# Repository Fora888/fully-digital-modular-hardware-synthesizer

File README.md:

# Fully digital modular synthesizer
A fully digital modular synthesizer specification

## Specification

### Audio data format
The audio data is transmitted and processed at 44.1kHz sample rate and 16 Bits of resolution

### Data transmission
Data transmission utilizes UART in combination with a simple protocol.
UART is configured at a baud rate of 2,000,000 with 8 data bits, 1 stop bit, no flow control and regular polarity. Signal levels are defined as 0V for low and 3.3V for high. However, all inputs and outputs should withstand voltages from +12V to -12V to prevent accidental damage when interfaced with analog equipment.
Due to UART's limitation of transmitting only 8 bits at a time and each audio sample requiring 16 bits, each sample is transmitted as three sequential packets. Each packet consists of 6 data bits followed by 2 order bits. Therefore a full UART frame looks like the following:
|1|6|2|1|
|-|-|-|-|
|Start bit|Data bits|Order bits|Stop bit|

The least significant 8 bits of a sample are sent first with order bits '00', followed by the middle 8 bits with order bits '10', and finally the most significant 4 bits with order bits '01'. The last two data bits of the last packet with order bits '01', as well as the order bit combination '11', remain unused for now but could be utilized for future extensions.

### Power
Modules are connected to +5V and ground via a 6 pin, 2 row, 2.54mm (0.1 inch) spacing header connector. These use the following pinout:

| | | |
| ------------- | ------------- | --------- |
| 5v  | 5v  | GND |
| GND | GND | GND |

This asymmetric pattern ensures, that in case the header is plugged in incorrectly, the power supply is short-circuited  and the module doesn't get damaged. Therefore it is advisable for power supplys to feature some sort of fusing mechanism.
Since noisy power doesn't impact the sound quality of digital audio, switching power supplys are sufficient for voltage conversion

### Mechanical
Since UART necessitates only one cable for transmission, akin to mono audio, the mechanical specifications of virtually any existing analog modular synthesizer can be used. The examples are based on eurorack the eurorack specification with 128mm height and 3.5mm TS (mono) phone connectors.

## Comparison to analog

### Advantages
**Less noise** - Digital transmission ensures that the audio signal is received exactly as it was sent, without introducing noise during transmission. Furthermore many analog modules use analog-to-digital and digital-to-analog conversion, which introduce noise into the signal

**Reduced complexity** - Digital signals don't require clean power or buffering in order to deliver good audio. Merely two diodes and one or two resistors, which are always in the exact same configuration, are required per input or output. In addition all I/O is full 16 bit and the audio is inherently DC coupled.

**Lower Price** - Microprocessors are cheap and require relatively few and simple auxiliary components when compared to analog electronics. The reduced complexity of digital signal processing also leads to lower development costs.

### Disadvantages
**Latency** - Digital signal processing always comes with latency. In case of the examples, where audio is processed in blocks of 128 samples, this latency comes in at ~3 ms per module. Fast processors can however reduce the block size, reducing the latency to half of that or even less.

**Module selection** - The digital protocol described is still in its early stages of development and therefore there are no manufacturers for it yet. So the only way to use it is to build your own modules

## Implementations and examples
An implementation for the teensy audio library as well as several example modules can be found in the [Teensy](https://github.com/Fora888/fully-digital-modular-hardware-synthesizer/tree/main/Teensy) folder.

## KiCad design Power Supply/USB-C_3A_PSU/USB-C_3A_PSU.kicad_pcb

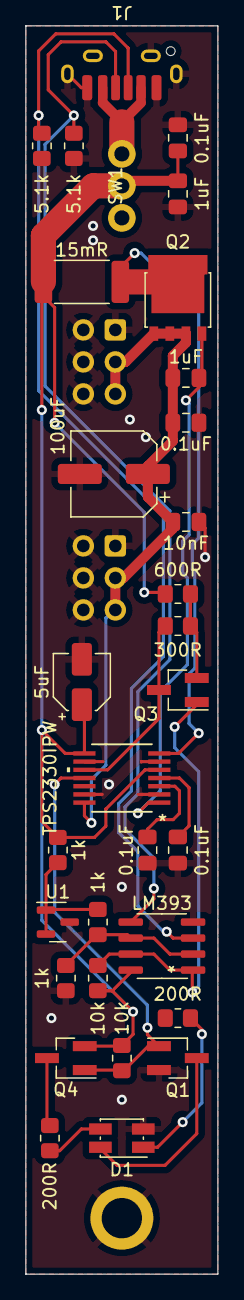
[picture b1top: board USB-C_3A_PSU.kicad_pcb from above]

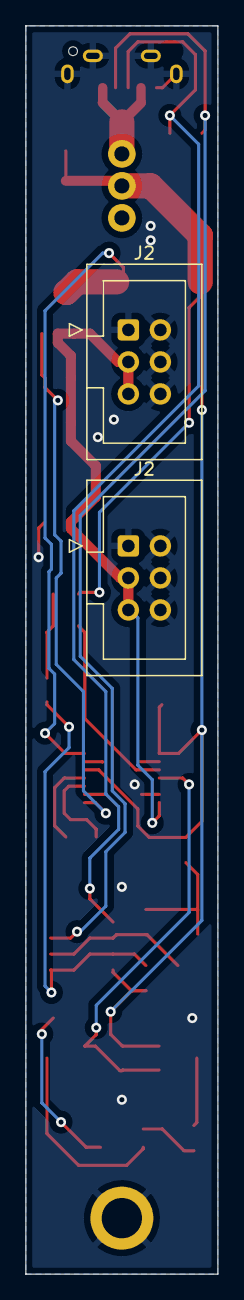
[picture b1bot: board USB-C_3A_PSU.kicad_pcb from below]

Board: 2 copper layers, 15.2 x 99.1 mm, 33 parts (2 on the bottom side), 20 nets.

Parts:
C1, C2, C4, C8: 0.1uF; C_0805_2012Metric_Pad1.18x1.45mm_HandSolder
C3, C5: 1uF; C_0805_2012Metric_Pad1.18x1.45mm_HandSolder
C6: 5uF; CP_Elec_4x5.4
C7: 10nF; C_0805_2012Metric_Pad1.18x1.45mm_HandSolder
C9: 100uF; CP_Elec_6.3x7.7
D1: LED_Dual_AKAK; LED_Kingbright_AAA3528ESGCT
J1: USB_C_Receptacle_USB2.0; USB_C_6Pin_Vert
J2, J2#2: Conn_02x03_Odd_Even; IDC-Header_2x03_P2.54mm_Vertical
Q1: Q_NMOS_GSD; SOT-23_Handsoldering
Q2: Q_NMOS_GSD; LFPAK56
Q3, Q4: Q_PMOS_GSD; SOT-23_Handsoldering
R1, R2: 5.1k; R_0805_2012Metric_Pad1.20x1.40mm_HandSolder
R3, R4, R5: 1k; R_0805_2012Metric_Pad1.20x1.40mm_HandSolder
R6, R12: 10k; R_0805_2012Metric_Pad1.20x1.40mm_HandSolder
R7: 15mR; R_2512_6332Metric_Pad1.40x3.35mm_HandSolder
R8: 600R; R_0805_2012Metric_Pad1.20x1.40mm_HandSolder
R9, R11: 200R; R_0805_2012Metric_Pad1.20x1.40mm_HandSolder
R10: 300R; R_0805_2012Metric_Pad1.20x1.40mm_HandSolder
SW1: SW_SPST; Miniature SPDT Toggle
U1: TL431DBZ; SOT-23
U2: LM393; SOIC-8_3.9x4.9mm_P1.27mm
U3: TPS2330IPW; PW14-M

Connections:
/1.25v Ref: R4.1, R5.1, U2.2 (-), U2.6 (_)
/5v In: C3.2, C4.2, C6.1, Q4.2 (S), R3.2, R6.1, R7.1, R8.1, R11.1, R12.2, SW1.2 (B), U2.8 (V+), U3.5 (VSENSE), U3.8 (IN)
/5v Out: C5.2, C7.1, C8.1, C9.1, J2.3, J2.5, J2#2.3, J2#2.5, Q2.2 (S), U3.14 (DISCH)
GND: C1.2, C2.2, C3.1, C4.1, C6.2, C7.2, C8.2, C9.2, D1.4 (K2), J1.A12 (GND), J1.B12 (GND), J1.S1 (SHIELD), J2.1, J2.2, J2.4, J2.6, J2#2.1, J2#2.2, J2#2.4, J2#2.6, Q1.2 (S), R1.2, R2.2, R5.2, U1.3 (A), U2.4 (V-), U3.2 (DGND), U3.6 (AGND), U3.9 (AGND), U3.13 (*ENABLE)
unnamed: C1.1, U3.3 (TIMER)
unnamed: C2.1, U3.4 (VREG)
unnamed: C5.1, Q2.1 (G), U3.1 (GATE)
unnamed: D1.1 (A1), R11.2
unnamed: D1.2 (K1), Q1.3 (D)
unnamed: D1.3 (A2), R9.2
unnamed: J1.A9 (VBUS), J1.B9 (VBUS), SW1.1 (A)
unnamed: J1.A5 (CC1), R2.1, U2.3 (+)
unnamed: J1.B5 (CC2), R1.1, U2.5 (+)
unnamed: Q1.1 (G), Q4.1 (G), R12.1, U3.11 (*FAULT)
unnamed: Q2.3 (D), R7.2, U3.7 (ISENSE)
unnamed: Q3.1 (G), R6.2, U2.1, U2.7
unnamed: Q3.2 (S), R8.2, R10.1
unnamed: Q3.3 (D), R10.2, U3.10 (ISET)
unnamed: Q4.3 (D), R9.1
unnamed: R3.1, R4.2, U1.1 (K), U1.2 (REF)

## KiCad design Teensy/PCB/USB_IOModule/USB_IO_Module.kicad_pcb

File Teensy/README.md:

# Teensy audio library extension
## TeensyDigitalModularExtension
This folder is a arduino library, which contains an implementation of the protocol as input and output blocks for the teensy audio library, as well as arduino sketches and auxiliary blocks for several example modules listed below. The library can easily be imported with the zip file and the following guide: https://docs.arduino.cc/software/ide-v1/tutorials/installing-libraries/.

## PCB
This folder contains PCBs as well as panel designs for the example modules. All PCBs use 2.54mm spacing between components, which means you can also build these modules on perfboard and connect the components with wire, instead of ordering PCBs

### VCA

### ADSR envelope generator

### Wavetable oscillator

### USB I/O

### Analog I/O

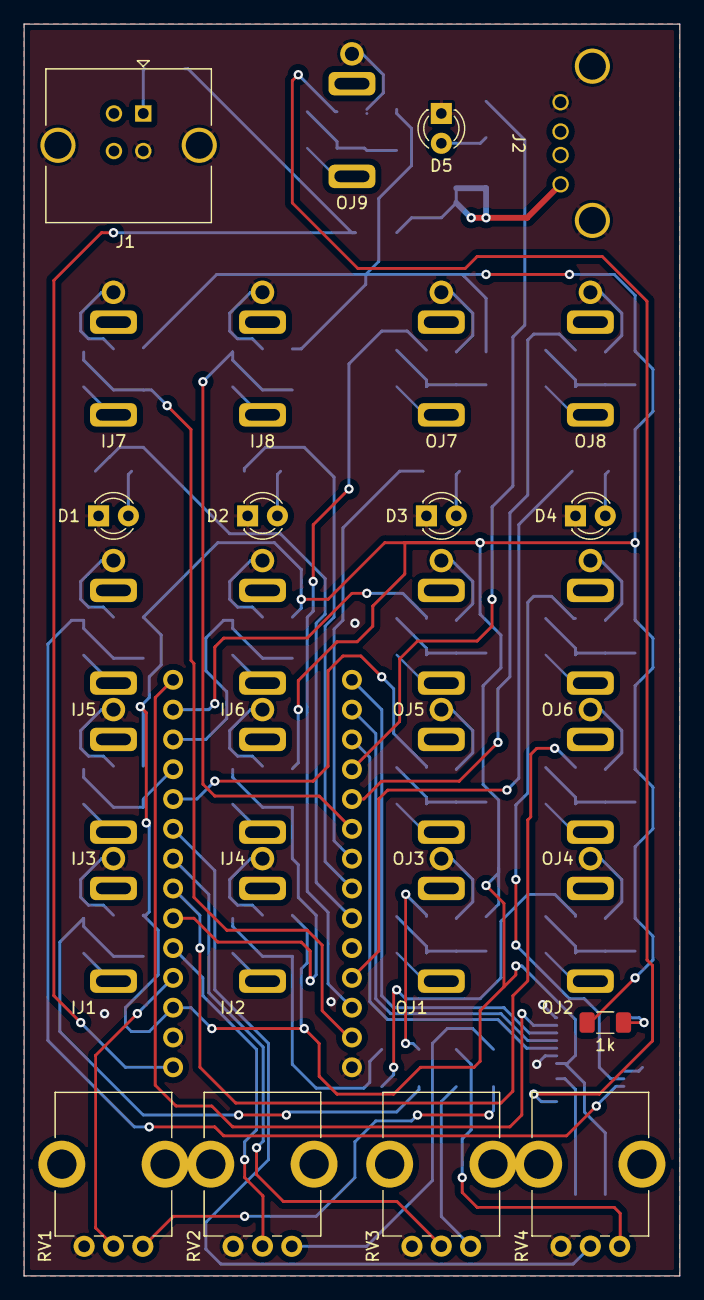
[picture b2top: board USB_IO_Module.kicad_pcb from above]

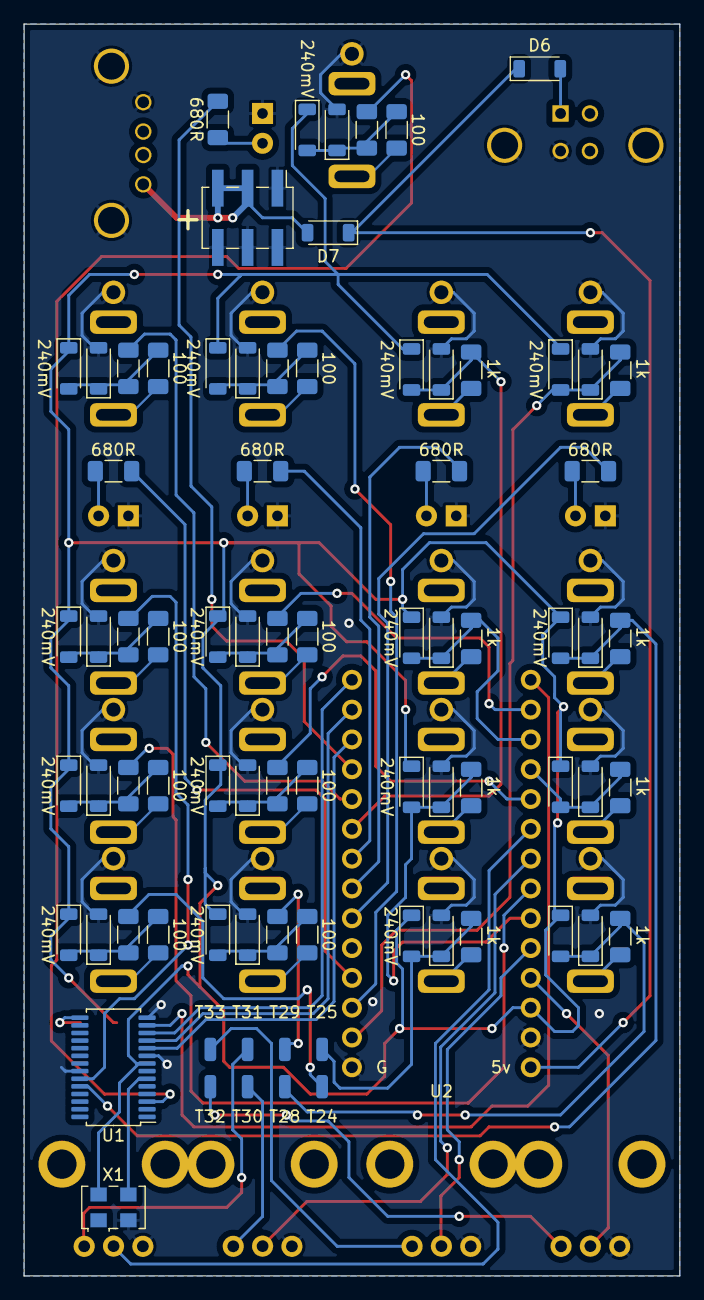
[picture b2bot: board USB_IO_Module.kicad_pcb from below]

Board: 2 copper layers, 55.9 x 106.7 mm, 101 parts (72 on the bottom side), 72 nets.

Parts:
D1, D2, D3, D4, D5: LED; LED_D3.0mm
D6, D7: 240mV; D_SOD-123 Handsolder
ID1, ID2, ID3, ID4, ID5, ID6, ID7, ID8, ID9, ID10, ID11, ID12, ID13, ID14, ID15, ID16: 240mV; D_SOD-123 Handsolder
IJ1, IJ2, IJ3, IJ4, IJ5, IJ6, IJ7, IJ8: Input; 3.5mm Jack Perfboard
IR1, IR2, IR3, IR4, IR5, IR6, IR7, IR8: 1k; R_1206_3216Metric_Pad1.30x1.75mm_HandSolder
J1: USB_B; USB_B_TE_5787834_Vertical
J2: USB_A; USB_A_Upright
J3: Power_Connector_2x3; PinHeader_2x03_P2.54mm_Vertical_SMD
OD1, OD2, OD3, OD4, OD5, OD6, OD7, OD8, OD9, OD10, OD11, OD12, OD13, OD14, OD15, OD16, OD17, OD18: 240mV; D_SOD-123 Handsolder
OJ1, OJ2, OJ3, OJ4, OJ5, OJ6, OJ7, OJ8, OJ9: Input; 3.5mm Jack Perfboard
OR1, OR3, OR5, OR7, OR9, OR11, OR13, OR15, OR17: 100; R_1206_3216Metric_Pad1.30x1.75mm_HandSolder
OR2, OR4, OR6, OR8, OR10, OR12, OR14, OR16, OR18: 900; R_1206_3216Metric_Pad1.30x1.75mm_HandSolder
R1: 1k; R_1206_3216Metric_Pad1.30x1.75mm_HandSolder
R2, R3, R4, R5, R6: 680R; R_1206_3216Metric_Pad1.30x1.75mm_HandSolder
RV1: Channel_1_Mod_Input_Gain; Bourns_PTV09A-4020UB103
RV2: Channel_2_Mod_Input_Gain; Bourns_PTV09A-4020UB103
RV3: Channel_1_Mod_Output_Gain; Bourns_PTV09A-4020UB103
RV4: Channel_2_Mod_Output_Gain; Bourns_PTV09A-4020UB103
U1: SC16IS762IPW; TSSOP-28_4.4x9.7mm_P0.65mm
U2: Teensy4.0; Teensy 4.0 horizontal
U2#2: Teensy4.0; Teensy 4.0 back pins
X1: XO53; Oscillator_SMD_EuroQuartz_XO53-4Pin_5.0x3.2mm

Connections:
+3.3V: ID2.1 (K), ID4.1 (K), ID6.1 (K), ID8.1 (K), ID10.1 (K), ID12.1 (K), ID14.1 (K), ID16.1 (K), OD2.1 (K), OD4.1 (K), OD6.1 (K), OD8.1 (K), OD10.1 (K), OD12.1 (K), OD14.1 (K), OD16.1 (K), OD18.1 (K), R1.1, U1.8 (VDD), U2.31 (3V3), X1.4 (V+)
+5V: D6.1 (K), D7.1 (K), U2.33 (VIN)
/RXB: ID9.1 (K), ID10.2 (A), IR5.2, U1.24 (RXB)
/T0: ID13.1 (K), ID14.2 (A), IR7.2, U2.2 (0_RX1_CRX2_CS1)
/T1: OR14.2, U2.3 (1_TX1_CTX2_MISO1)
/T2: R5.1, U2.4 (2_OUT2)
/T4: R2.1, U2.6 (4_BCLK2)
/T5: R3.1, U2.7 (5_IN2)
/T6: R4.1, U2.8 (6_OUT1D)
/T7: ID15.1 (K), ID16.2 (A), IR8.2, U2.9 (7_RX2_OUT1A)
/T8: OR16.2, U2.10 (8_TX2_IN1)
/T9: R6.1, U2.11 (9_OUT1C)
/T10: U1.10 (A0/~CS), U2.12 (10_CS_MQSR)
/T11: U1.11 (A1/SI), U2.13 (11_MOSI_CTX1)
/T12: U1.12 (n.c./SO), U2.14 (12_MISO_MQSL)
/T13: U1.13 (SCL/SCLK), U2.20 (13_SCK_CRX1_LED)
/T14: OR10.2, U2.21 (14_A0_TX3_SPDIF_OUT)
/T15: ID11.1 (K), ID12.2 (A), IR6.2, U2.22 (15_A1_RX3_SPDIF_IN)
/T16: ID5.1 (K), ID6.2 (A), IR3.2, U2.23 (16_A2_RX4_SCL1)
/T17: OR6.2, U2.24 (17_A3_TX4_SDA1)
/T18: RV4.2, U2.25 (18_A4_SDA0)
/T19: RV3.2, U2.26 (19_A5_SCL0)
/T20: OR8.2, U2.27 (20_A6_TX5_LRCLK1)
/T21: ID7.1 (K), ID8.2 (A), IR4.2, U2.28 (21_A7_RX5_BCLK1)
/T22: RV2.2, U2.29 (22_A8_CTX1)
/T23: RV1.2, U2.30 (23_A9_CRX1_MCLK1)
/T24: OR4.2, U2#2.35 (24_A10_TX6_SCL2)
/T25: ID3.1 (K), ID4.2 (A), IR2.2, U2#2.36 (25_A11_RX6_SDA2)
/T28: ID1.1 (K), ID2.2 (A), IR1.2, U2#2.39 (28_RX7)
/T29: OR2.2, U2#2.40 (29_TX7)
/T30: RV3.1, U2#2.41 (30_CRX3)
/T31: RV4.1, U2#2.42 (31_CTX3)
/T32: RV1.1, U2#2.43 (32_OUT1B)
/T33: RV2.1, U2#2.44 (33_MCLK2)
/TXA: OR18.2, U1.3 (TXA)
/TXB: OR12.2, U1.23 (TXB)
GND: D1.1 (K), D2.1 (K), D3.1 (K), D4.1 (K), D5.1 (K), ID1.2 (A), ID3.2 (A), ID5.2 (A), ID7.2 (A), ID9.2 (A), ID11.2 (A), ID13.2 (A), ID15.2 (A), IJ1.G, IJ2.G, IJ3.G, IJ4.G, IJ5.G, IJ6.G, IJ7.G, IJ8.G, J1.4 (GND), J1.5 (Shield), J2.4 (GND), J2.5 (Shield), J3.1, J3.2, J3.4, J3.6, OD1.2 (A), OD3.2 (A), OD5.2 (A), OD7.2 (A), OD9.2 (A), OD11.2 (A), OD13.2 (A), OD15.2 (A), OD17.2 (A), OJ1.G, OJ2.G, OJ3.G, OJ4.G, OJ5.G, OJ6.G, OJ7.G, OJ8.G, OJ9.G, RV1.3, RV2.3, RV3.3, RV4.3, U1.9 (I2C/~SPI), U1.14 (SDA/VSS), U1.22 (VSS), U2.1 (GND), U2.32 (GND), X1.2 (GND)
unnamed: D1.2 (A), R2.2
unnamed: D2.2 (A), R3.2
unnamed: D3.2 (A), R4.2
unnamed: D4.2 (A), R5.2
unnamed: D5.2 (A), R6.2
unnamed: D6.2 (A), J1.1 (VBUS)
unnamed: D7.2 (A), J2.1 (VBUS), J3.3, J3.5
unnamed: IJ1.T, IR1.1
unnamed: IJ2.T, IR2.1
unnamed: IJ3.T, IR3.1
unnamed: IJ4.T, IR4.1
unnamed: IJ5.T, IR5.1
unnamed: IJ6.T, IR6.1
unnamed: IJ7.T, IR7.1
unnamed: IJ8.T, IR8.1
unnamed: OD1.1 (K), OD2.2 (A), OR1.2, OR2.1
unnamed: OD3.1 (K), OD4.2 (A), OR3.2, OR4.1
unnamed: OD5.1 (K), OD6.2 (A), OR5.2, OR6.1
unnamed: OD7.1 (K), OD8.2 (A), OR7.2, OR8.1
unnamed: OD9.1 (K), OD10.2 (A), OR9.2, OR10.1
unnamed: OD11.1 (K), OD12.2 (A), OR11.2, OR12.1
unnamed: OD13.1 (K), OD14.2 (A), OR13.2, OR14.1
unnamed: OD15.1 (K), OD16.2 (A), OR15.2, OR16.1
unnamed: OD17.1 (K), OD18.2 (A), OR17.2, OR18.1
unnamed: OJ1.T, OR1.1
unnamed: OJ2.T, OR3.1
unnamed: OJ3.T, OR5.1
unnamed: OJ4.T, OR7.1
unnamed: OJ5.T, OR9.1
unnamed: OJ6.T, OR11.1
unnamed: OJ7.T, OR13.1
unnamed: OJ8.T, OR15.1
unnamed: OJ9.T, OR17.1
unnamed: R1.2, U1.15 (~IRQ)
unnamed: U1.6 (XTAL1), X1.3 (OUT)

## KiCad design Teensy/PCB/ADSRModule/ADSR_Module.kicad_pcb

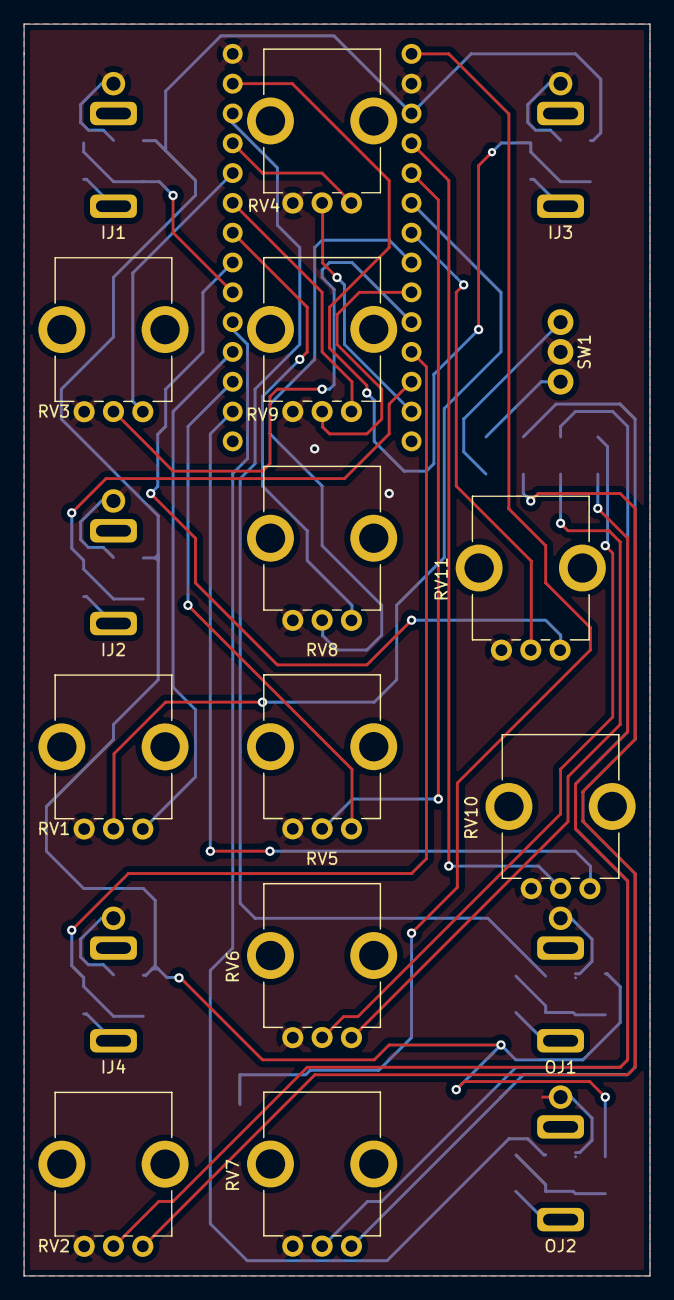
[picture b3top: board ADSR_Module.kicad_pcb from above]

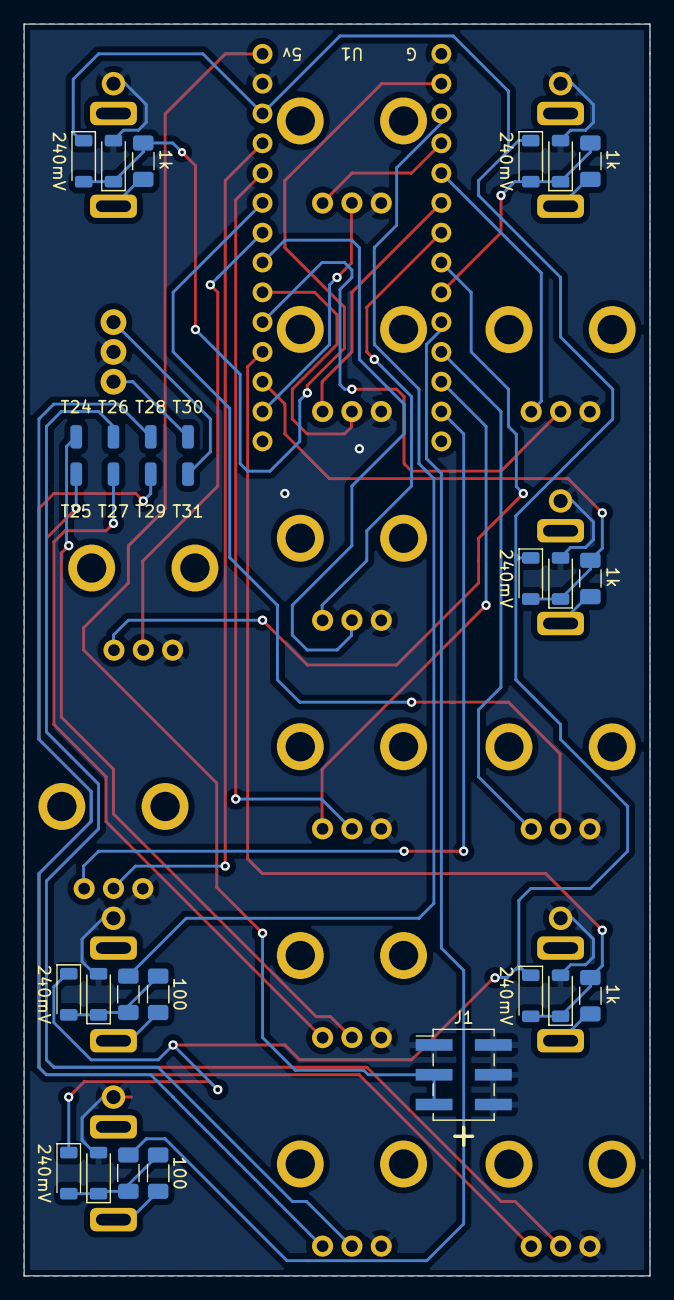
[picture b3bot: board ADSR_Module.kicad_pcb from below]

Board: 2 copper layers, 53.3 x 106.7 mm, 41 parts (23 on the bottom side), 41 nets.

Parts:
ID1, ID2, ID3, ID4, ID5, ID6, ID7, ID8: 240mV; D_SOD-123 Handsolder
IJ1, IJ2, IJ3, IJ4: Input; 3.5mm Jack Perfboard
IR1, IR2, IR3, IR4: 1k; R_1206_3216Metric_Pad1.30x1.75mm_HandSolder
J1: Power_Connector_2x3; PinHeader_2x03_P2.54mm_Vertical_SMD
OD1, OD2, OD3, OD4: 240mV; D_SOD-123 Handsolder
OJ1, OJ2: Input; 3.5mm Jack Perfboard
OR1, OR3: 100; R_1206_3216Metric_Pad1.30x1.75mm_HandSolder
OR2, OR4: 900; R_1206_3216Metric_Pad1.30x1.75mm_HandSolder
RV1: Decay_Time_Mod_Scale; Bourns_PTV09A-4020UB103
RV2: Release_Time_Mod_Scale; Bourns_PTV09A-4020UB103
RV3: Attack_Time_Mod_Scale; Bourns_PTV09A-4020UB103
RV4: Attack_Slope; Bourns_PTV09A-4020UB103
RV5: Decay_Time_Offset; Bourns_PTV09A-4025FB103
RV6: Release_Slope; Bourns_PTV09A-4020UB103
RV7: Release_Time_Offset; Bourns_PTV09A-4025FB103
RV8: Decay_Slope; Bourns_PTV09A-4020UB103
RV9: Attack_Time_Offset; Bourns_PTV09A-4025FB103
RV10: Output_Scale; Bourns_PTV09A-4020UB103
RV11: Sustain_Offset; Bourns_PTV09A-4020UB103
SW1: Mode_Switch; Miniature SPDT Toggle
U1: Teensy4.0; Teensy 4.0 horizontal
U1#2: Teensy4.0; Teensy 4.0 back pins

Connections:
+3.3V: ID2.1 (K), ID4.1 (K), ID6.1 (K), ID8.1 (K), OD2.1 (K), OD4.1 (K), U1.31 (3V3)
+5V: J1.3, J1.5, U1.33 (VIN)
/T0: ID5.1 (K), ID6.2 (A), IR3.2, U1.2 (0_RX1_CRX2_CS1)
/T1: OR2.2, U1.3 (1_TX1_CTX2_MISO1)
/T2: RV4.1, U1.4 (2_OUT2)
/T3: RV3.1, U1.5 (3_LRCLK2)
/T4: RV9.1, U1.6 (4_BCLK2)
/T5: RV8.1, U1.7 (5_IN2)
/T6: RV11.1, U1.8 (6_OUT1D)
/T7: ID1.1 (K), ID2.2 (A), IR1.2, U1.9 (7_RX2_OUT1A)
/T8: OR4.2, U1.10 (8_TX2_IN1)
/T9: RV1.1, U1.11 (9_OUT1C)
/T10: RV5.1, U1.12 (10_CS_MQSR)
/T11: RV10.1, U1.13 (11_MOSI_CTX1)
/T14: RV4.2, U1.21 (14_A0_TX3_SPDIF_OUT)
/T15: ID3.1 (K), ID4.2 (A), IR2.2, U1.22 (15_A1_RX3_SPDIF_IN)
/T16: ID7.1 (K), ID8.2 (A), IR4.2, U1.23 (16_A2_RX4_SCL1)
/T17: RV3.2, U1.24 (17_A3_TX4_SDA1)
/T18: RV9.2, U1.25 (18_A4_SDA0)
/T19: RV8.2, U1.26 (19_A5_SCL0)
/T20: RV11.2, U1.27 (20_A6_TX5_LRCLK1)
/T21: RV1.2, U1.28 (21_A7_RX5_BCLK1)
/T22: RV5.2, U1.29 (22_A8_CTX1)
/T23: RV10.2, U1.30 (23_A9_CRX1_MCLK1)
/T24: RV6.2, U1#2.35 (24_A10_TX6_SCL2)
/T25: RV2.2, U1#2.36 (25_A11_RX6_SDA2)
/T26: RV7.2, U1#2.37 (26_A12_MOSI1)
/T27: RV6.1, U1#2.38 (27_A13_SCK1)
/T28: RV7.1, U1#2.39 (28_RX7)
/T29: RV2.1, U1#2.40 (29_TX7)
/T30: SW1.3, U1#2.41 (30_CRX3)
/T31: SW1.1, U1#2.42 (31_CTX3)
GND: ID1.2 (A), ID3.2 (A), ID5.2 (A), ID7.2 (A), IJ1.G, IJ2.G, IJ3.G, IJ4.G, J1.1, J1.2, J1.4, J1.6, OD1.2 (A), OD3.2 (A), OJ1.G, OJ2.G, RV1.3, RV2.3, RV3.3, RV4.3, RV5.3, RV6.3, RV7.3, RV8.3, RV9.3, RV10.3, RV11.3, SW1.2, U1.1 (GND), U1.32 (GND)
unnamed: IJ1.T, IR1.1
unnamed: IJ2.T, IR2.1
unnamed: IJ3.T, IR3.1
unnamed: IJ4.T, IR4.1
unnamed: OD1.1 (K), OD2.2 (A), OR1.2, OR2.1
unnamed: OD3.1 (K), OD4.2 (A), OR3.2, OR4.1
unnamed: OJ1.T, OR1.1
unnamed: OJ2.T, OR3.1

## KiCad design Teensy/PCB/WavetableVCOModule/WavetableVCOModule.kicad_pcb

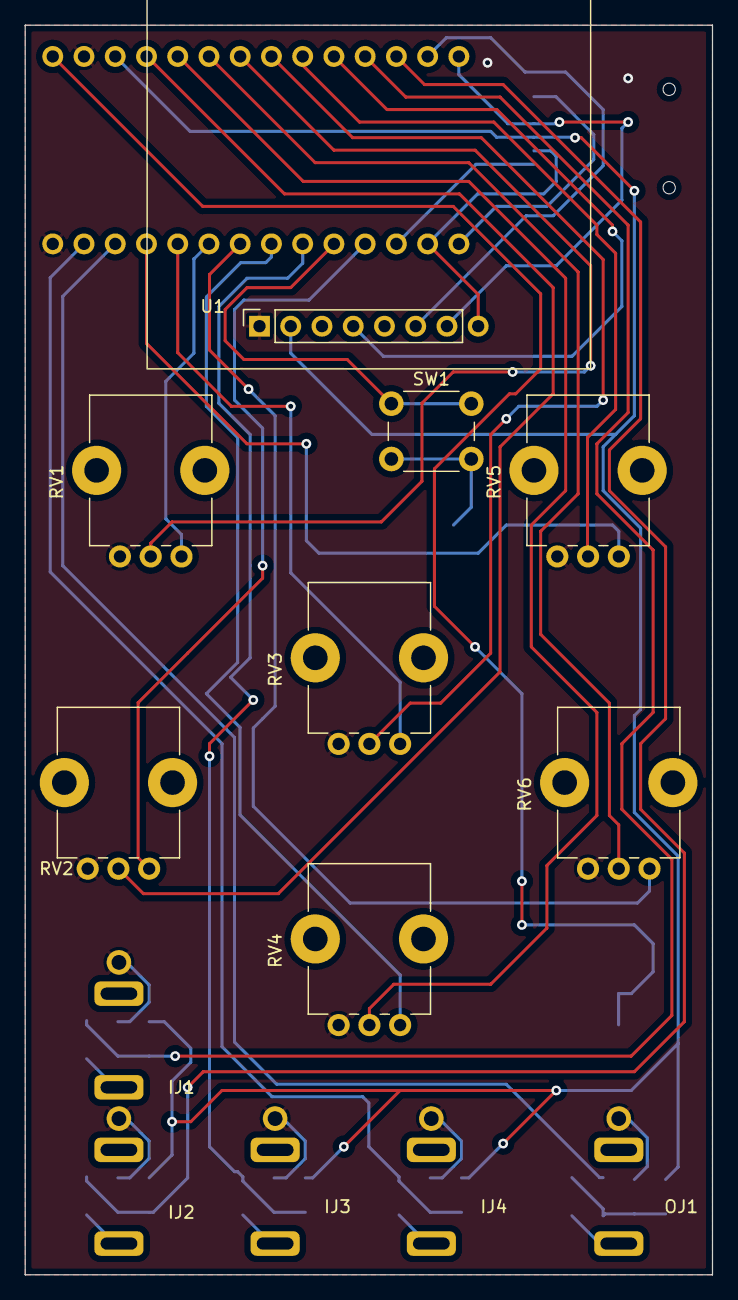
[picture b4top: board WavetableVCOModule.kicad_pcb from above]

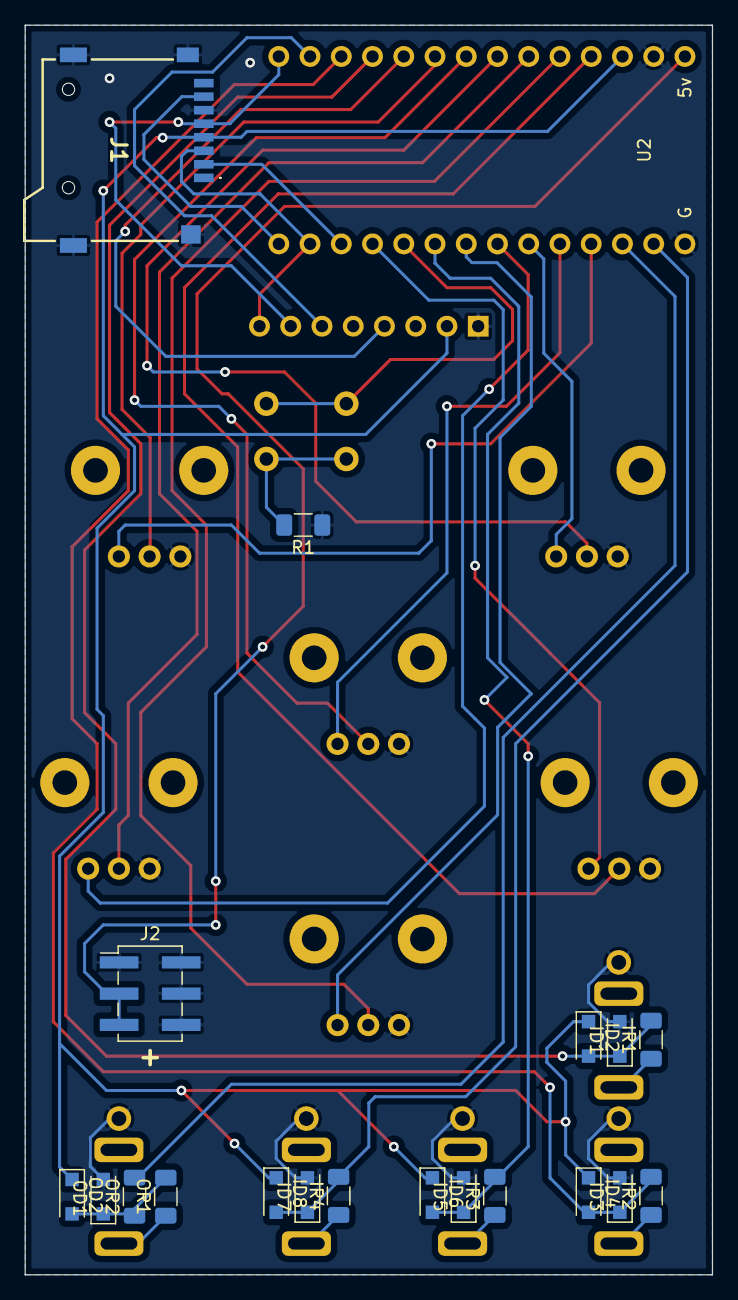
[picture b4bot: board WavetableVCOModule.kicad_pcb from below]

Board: 2 copper layers, 55.9 x 101.6 mm, 33 parts (20 on the bottom side), 34 nets.

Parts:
ID1, ID2, ID3, ID4, ID5, ID6, ID7, ID8: 240mV; D_SOD-123F
IJ1, IJ2, IJ3, IJ4: Input; 3.5mm Jack Perfboard
IR1, IR2, IR3, IR4: 1k; R_1206_3216Metric_Pad1.30x1.75mm_HandSolder
J1: Micro_SD_Card; MSD4A
J2: Power_Connector_2x3; PinHeader_2x03_P2.54mm_Vertical_SMD
OD1, OD2: 240mV; D_SOD-123F
OJ1: Input; 3.5mm Jack Perfboard
OR1: 100; R_1206_3216Metric_Pad1.30x1.75mm_HandSolder
OR2: 900; R_1206_3216Metric_Pad1.30x1.75mm_HandSolder
R1: 10k; R_1206_3216Metric_Pad1.30x1.75mm_HandSolder
RV1: Warp_Offset_Pot; Bourns_PTV09A-4025FB103
RV2: Warp_Scale_Pot; Bourns_PTV09A-4020UB103
RV3: Frequency_Offset_Pot; Bourns_PTV09A-4025FB103
RV4: FM_Scale_Pot; Bourns_PTV09A-4020UB103
RV5: Position_Offset_Pot; Bourns_PTV09A-4025FB103
RV6: Position_Scale_Pot; Bourns_PTV09A-4020UB103
SW1: Next_File_Button; SW_PUSH_6mm_H13mm
U1: SPI_Oled; 1.5_inch_Oled
U2: Teensy4.0; Teensy 4.0 horizontal

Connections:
+3.3V: ID2.1 (K), ID4.1 (K), ID6.1 (K), ID8.1 (K), J1.4 (VDD), OD2.1 (K), U1.6 (VIN), U2.31 (3V3)
+5V: J2.3, J2.5, U2.33 (VIN)
/T0: ID7.1 (K), ID8.2 (A), IR4.2, U2.2 (0_RX1_CRX2_CS1)
/T1: OR2.2, U2.3 (1_TX1_CTX2_MISO1)
/T2: RV5.1, U2.4 (2_OUT2)
/T3: RV3.1, U2.5 (3_LRCLK2)
/T4: RV1.1, U2.6 (4_BCLK2)
/T5: RV6.1, U2.7 (5_IN2)
/T6: RV4.1, U2.8 (6_OUT1D)
/T7: ID5.1 (K), ID6.2 (A), IR3.2, U2.9 (7_RX2_OUT1A)
/T8: SW1.1, U2.10 (8_TX2_IN1)
/T9: RV2.1, U2.11 (9_OUT1C)
/T10: J1.2 (DAT3/CD), U2.12 (10_CS_MQSR)
/T11: J1.3 (CMD), U1.1 (DATA), U2.13 (11_MOSI_CTX1)
/T12: J1.7 (DAT0), U2.14 (12_MISO_MQSL)
/T13: J1.5 (CLK), U1.2 (CLK), U2.20 (13_SCK_CRX1_LED)
/T14: U1.3 (D/C), U2.21 (14_A0_TX3_SPDIF_OUT)
/T15: ID3.1 (K), ID4.2 (A), IR2.2, U2.22 (15_A1_RX3_SPDIF_IN)
/T16: ID1.1 (K), ID2.2 (A), IR1.2, U2.23 (16_A2_RX4_SCL1)
/T17: U1.5 (CS), U2.24 (17_A3_TX4_SDA1)
/T18: RV5.2, U2.25 (18_A4_SDA0)
/T19: RV3.2, U2.26 (19_A5_SCL0)
/T20: RV1.2, U2.27 (20_A6_TX5_LRCLK1)
/T21: RV6.2, U2.28 (21_A7_RX5_BCLK1)
/T22: RV4.2, U2.29 (22_A8_CTX1)
/T23: RV2.2, U2.30 (23_A9_CRX1_MCLK1)
GND: ID1.2 (A), ID3.2 (A), ID5.2 (A), ID7.2 (A), IJ1.G, IJ2.G, IJ3.G, IJ4.G, J1.6 (VSS), J1.9 (SHIELD), J2.1, J2.2, J2.4, J2.6, OD1.2 (A), OJ1.G, R1.1, RV1.3, RV2.3, RV3.3, RV4.3, RV5.3, RV6.3, U1.7 (GND), U2.1 (GND), U2.32 (GND)
unnamed: IJ1.T, IR1.1
unnamed: IJ2.T, IR2.1
unnamed: IJ3.T, IR3.1
unnamed: IJ4.T, IR4.1
unnamed: OD1.1 (K), OD2.2 (A), OR1.2, OR2.1
unnamed: OJ1.T, OR1.1
unnamed: R1.2, SW1.2

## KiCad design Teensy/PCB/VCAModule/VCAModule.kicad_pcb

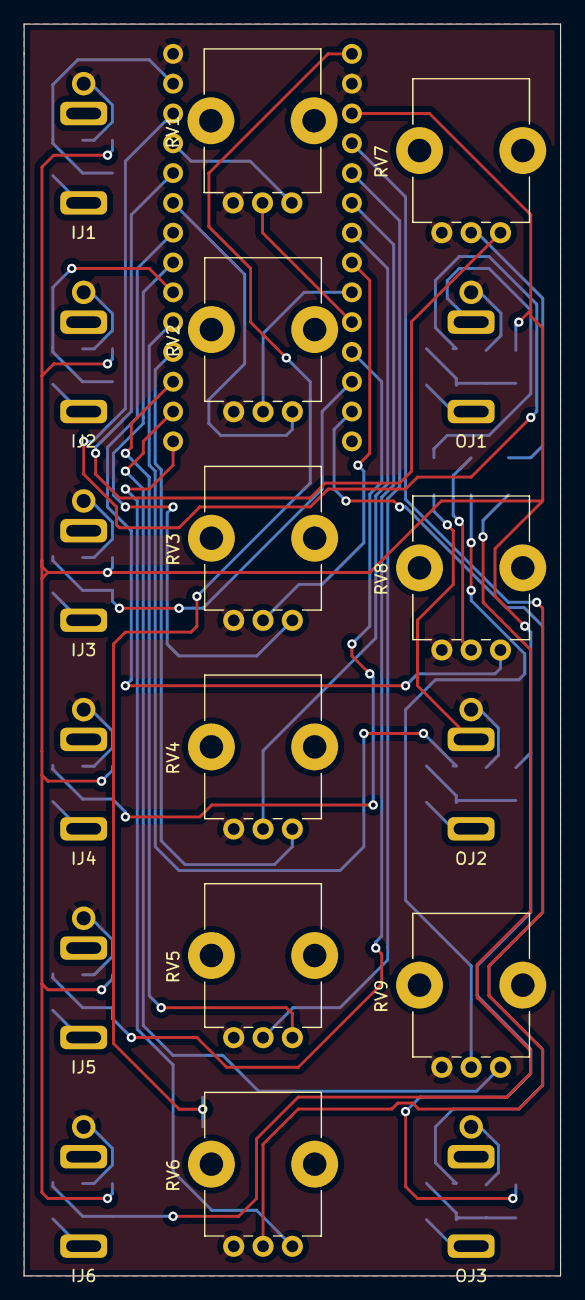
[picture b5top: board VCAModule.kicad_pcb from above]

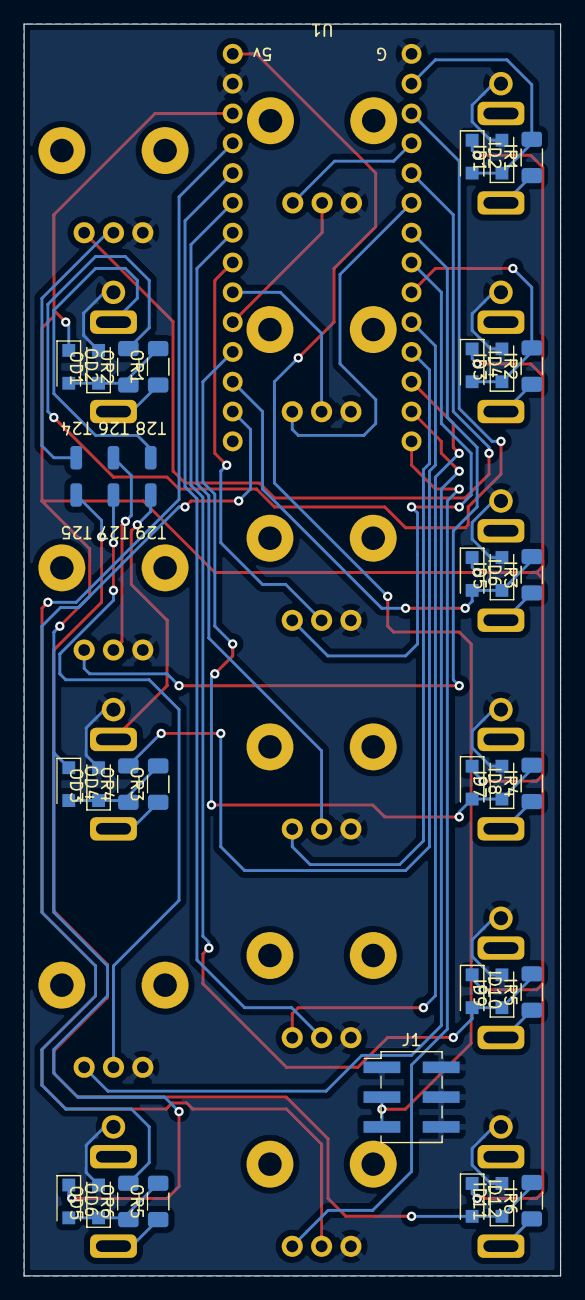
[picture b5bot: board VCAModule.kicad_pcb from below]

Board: 2 copper layers, 45.7 x 106.7 mm, 51 parts (33 on the bottom side), 44 nets.

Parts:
ID1, ID2, ID3, ID4, ID5, ID6, ID7, ID8, ID9, ID10, ID11, ID12: 240mV; D_SOD-123F
IJ1, IJ2, IJ3, IJ4, IJ5, IJ6: Input; 3.5mm Jack Perfboard
IR1, IR2, IR3, IR4, IR5, IR6: 1k; R_1206_3216Metric_Pad1.30x1.75mm_HandSolder
J1: Power_Connector_2x3; PinHeader_2x03_P2.54mm_Vertical_SMD
OD1, OD2, OD3, OD4, OD5, OD6: 240mV; D_SOD-123F
OJ1, OJ2, OJ3: Input; 3.5mm Jack Perfboard
OR1, OR3, OR5: 100; R_1206_3216Metric_Pad1.30x1.75mm_HandSolder
OR2, OR4, OR6: 900; R_1206_3216Metric_Pad1.30x1.75mm_HandSolder
RV1: CV_1_Slope; Bourns_PTV09A-4020UB103
RV2: CV_Scale_1; Bourns_PTV09A-4020UB103
RV3: CV_2_Slope; Bourns_PTV09A-4020UB103
RV4: CV_Scale_2; Bourns_PTV09A-4020UB103
RV5: CV_3_Slope; Bourns_PTV09A-4020UB103
RV6: CV_Scale_3; Bourns_PTV09A-4020UB103
RV7: VCA_1_Gain; Bourns_PTV09A-4025FB103
RV8: VCA_2_Gain; Bourns_PTV09A-4025FB103
RV9: VCA_3_Gain; Bourns_PTV09A-4025FB103
U1: Teensy4.0; Teensy 4.0 horizontal
U1#2: Teensy4.0; Teensy 4.0 back pins

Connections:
+3.3V: ID2.1 (K), ID4.1 (K), ID6.1 (K), ID8.1 (K), ID10.1 (K), ID12.1 (K), OD2.1 (K), OD4.1 (K), OD6.1 (K), U1.31 (3V3)
+5V: J1.3, J1.5, U1.33 (VIN)
/T0: ID1.1 (K), ID2.2 (A), IR1.2, U1.2 (0_RX1_CRX2_CS1)
/T1: OR2.2, U1.3 (1_TX1_CTX2_MISO1)
/T2: RV1.1, U1.4 (2_OUT2)
/T3: RV7.1, U1.5 (3_LRCLK2)
/T4: RV2.1, U1.6 (4_BCLK2)
/T5: RV8.1, U1.7 (5_IN2)
/T6: RV3.1, U1.8 (6_OUT1D)
/T7: ID3.1 (K), ID4.2 (A), IR2.2, U1.9 (7_RX2_OUT1A)
/T8: OR4.2, U1.10 (8_TX2_IN1)
/T9: RV4.1, U1.11 (9_OUT1C)
/T10: RV5.1, U1.12 (10_CS_MQSR)
/T11: RV9.1, U1.13 (11_MOSI_CTX1)
/T12: RV6.1, U1.14 (12_MISO_MQSL)
/T14: OR6.2, U1.21 (14_A0_TX3_SPDIF_OUT)
/T15: ID5.1 (K), ID6.2 (A), IR3.2, U1.22 (15_A1_RX3_SPDIF_IN)
/T16: ID7.1 (K), ID8.2 (A), IR4.2, U1.23 (16_A2_RX4_SCL1)
/T17: RV1.2, U1.24 (17_A3_TX4_SDA1)
/T18: RV2.2, U1.25 (18_A4_SDA0)
/T19: RV3.2, U1.26 (19_A5_SCL0)
/T20: RV4.2, U1.27 (20_A6_TX5_LRCLK1)
/T21: ID9.1 (K), ID10.2 (A), IR5.2, U1.28 (21_A7_RX5_BCLK1)
/T22: RV5.2, U1.29 (22_A8_CTX1)
/T23: RV6.2, U1.30 (23_A9_CRX1_MCLK1)
/T24: RV7.2, U1#2.35 (24_A10_TX6_SCL2)
/T25: ID11.1 (K), ID12.2 (A), IR6.2, U1#2.36 (25_A11_RX6_SDA2)
/T26: RV8.2, U1#2.37 (26_A12_MOSI1)
/T27: RV9.2, U1#2.38 (27_A13_SCK1)
/T28: OJ1.S, U1#2.39 (28_RX7)
/T29: OJ2.S, U1#2.40 (29_TX7)
GND: ID1.2 (A), ID3.2 (A), ID5.2 (A), ID7.2 (A), ID9.2 (A), ID11.2 (A), IJ1.G, IJ2.G, IJ3.G, IJ4.G, IJ5.G, IJ6.G, J1.1, J1.2, J1.4, J1.6, OD1.2 (A), OD3.2 (A), OD5.2 (A), OJ1.G, OJ2.G, OJ3.G, RV1.3, RV2.3, RV3.3, RV4.3, RV5.3, RV6.3, RV7.3, RV8.3, RV9.3, U1.1 (GND), U1.32 (GND)
unnamed: IJ1.T, IR1.1
unnamed: IJ2.T, IR2.1
unnamed: IJ3.T, IR3.1
unnamed: IJ4.T, IR4.1
unnamed: IJ5.T, IR5.1
unnamed: IJ6.T, IR6.1
unnamed: OD1.1 (K), OD2.2 (A), OR1.2, OR2.1
unnamed: OD3.1 (K), OD4.2 (A), OR3.2, OR4.1
unnamed: OD5.1 (K), OD6.2 (A), OR5.2, OR6.1
unnamed: OJ1.T, OR1.1
unnamed: OJ2.T, OR3.1
unnamed: OJ3.T, OR5.1

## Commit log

2024-05-06 Added library with implementation for teensy audio
2024-05-06 fixed folder structure
2024-05-06 Zipped stuff
2024-05-23 Added google confirmation of ownership
2024-05-23 Created github pages clone of repository for google verification
2024-05-23 Changed added correct base to index
2024-05-30 Fixed typo
2024-06-02 Added power specification
2024-06-07 Fixed Spelling
2024-06-07 Added ADSR PCB
2024-06-07 Removed github pages
2024-06-09 Fixed component names on schematic
2024-06-16 Added VCAModule PCB
2024-06-16 Added Images to README
2024-06-24 Added USB_IO module PCB
2024-06-24 Added USB_IO Images
2024-07-01 Replaced Schematic Lines with references
2024-07-10 Added Wavetable VCO
2024-07-11 Added Power connector and bracket
2024-07-21 Added Panel PCBs
2024-07-25 Generated Gerbers
2024-08-09 Improved ADSR module
2024-09-22 Made NPTH holes 0.5mm bigger; adjusted diode pads for better solderability
2024-10-26 Added USB-C Power Supply
